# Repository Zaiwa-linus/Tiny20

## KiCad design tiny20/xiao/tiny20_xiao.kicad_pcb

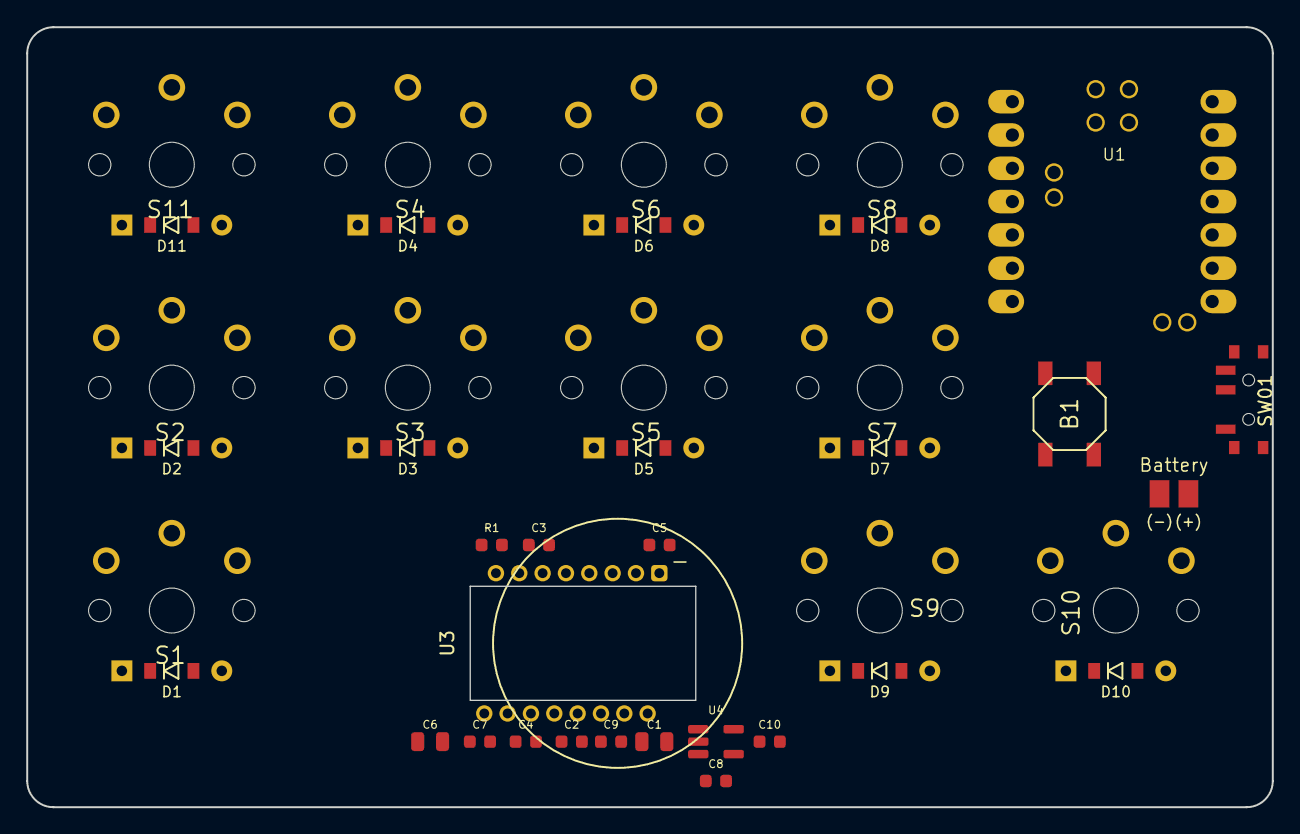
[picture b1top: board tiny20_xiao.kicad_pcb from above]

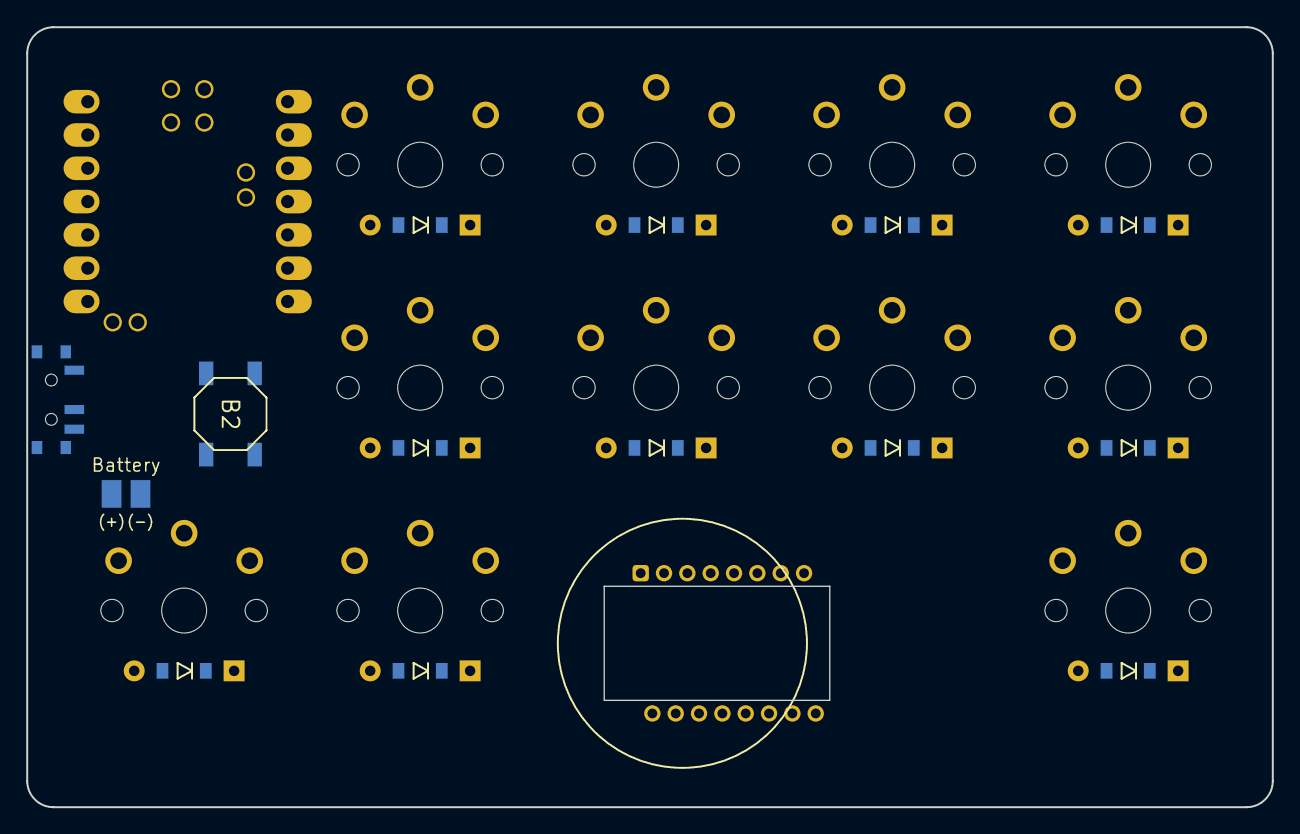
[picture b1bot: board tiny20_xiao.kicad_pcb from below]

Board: 2 copper layers, 95.0 x 59.5 mm, 41 parts (2 on the bottom side), 36 nets, no tracks yet.

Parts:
B1, B2: SW_TACT_ALPS_SKQGABE010
BT01: Battery_Cell; battery_pads_reversible
C1: 3.3uF; C_0805
C2, C3, C4: 100nF; C_0603
C5, C7: 10nF; C_0603
C6: 10uF; C_0805
C8, C9: 1uF; C_0603
C10: 22nF; C_0603
D1, D2, D3, D4, D5, D6, D7, D8, D9, D10, D11: 1N4148W; D_SOD123_THT_reversible
R1: 10k; R_0603
S1, S2, S3, S4, S5, S6, S7, S8, S9, S10, S11: chocV1_reversible
SW01: SW_SPDT; Power_reversible
TB1: Trackball 19mm; Trackball_19mm
U1: xiao-ble-thruhole; xiao-ble-tht
U3: PMW3610DM-SUDU; PMW3610DM-SUDU_16Pin
U4: TLV74318PDBVR; SOT-23-5_HandSoldering

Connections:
3V3: C3.1, C8.1, R1.1, U1.12, U3.6 (VDDIO), U4.1, U4.3
+1V8: C1.1, C2.1, C9.1, U3.14 (VDD), U4.5
GND: B1.2, B2.2, C1.2, C2.2, C3.2, C5.2, C6.2, C7.2, C8.2, C9.2, C10.2, U1.13, U1.18, U3.11 (GND), U4.2
K_S1: D1.2, S1.1
K_S2: D2.2, S2.1
K_S3: D3.2, S3.1
K_S4: D4.2, S4.1
K_S5: D5.2, S5.1
K_S6: D6.2, S6.1
K_S7: D7.2, S7.1
K_S8: D8.2, S8.1
K_S9: D9.2, S9.1
K_S10: D10.2, S10.1
K_S11: D11.2, S11.1
P1: D4.1, D6.1, D8.1, D11.1, U1.1
P2: D2.1, D3.1, D5.1, D7.1, U1.2
P3: D1.1, D9.1, D10.1, U1.3
P4: S1.2, S2.2, S11.2, U1.4
P5: S3.2, S4.2, S10.2, U1.5
P6: S5.2, S6.2, U1.6
P7: S7.2, S8.2, S9.2, U1.7
P8: U1.8, U3.3 (SCLK)
P9: U1.9, U3.2 (SDIO)
P10: U1.10, U3.8 (MOTION)
P11: U1.11, U3.5 (NCS)
P19: SW01.3, U1.19
P20: BT01.2, U1.20
RST: B1.1, B2.1, U1.17
TB_CN: C4.2, U3.13 (CN)
TB_CP: C4.1, U3.12 (CP)
TB_NR: C10.1, U4.4
TB_NRESET: R1.2, U3.7 (NRESET)
TB_VCP: C6.1, C7.1, U3.9 (VCP)
TB_VCSEL+: C5.1, U3.1 (+VCSEL), U3.10 (PASS_T)
TB_VCSEL-: U3.15 (XYLASER), U3.16 (-VCSEL)
pm: BT01.1, SW01.2

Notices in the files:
parts and their libraries:
PMW3610DM-SUDU molded lead-frame DIP in a PCB cutout, LM18-LSI lens. Optical center at (2.988,0). Geometry from siderakb/pmw3610-pcb (CERN-OHL-P v2).
